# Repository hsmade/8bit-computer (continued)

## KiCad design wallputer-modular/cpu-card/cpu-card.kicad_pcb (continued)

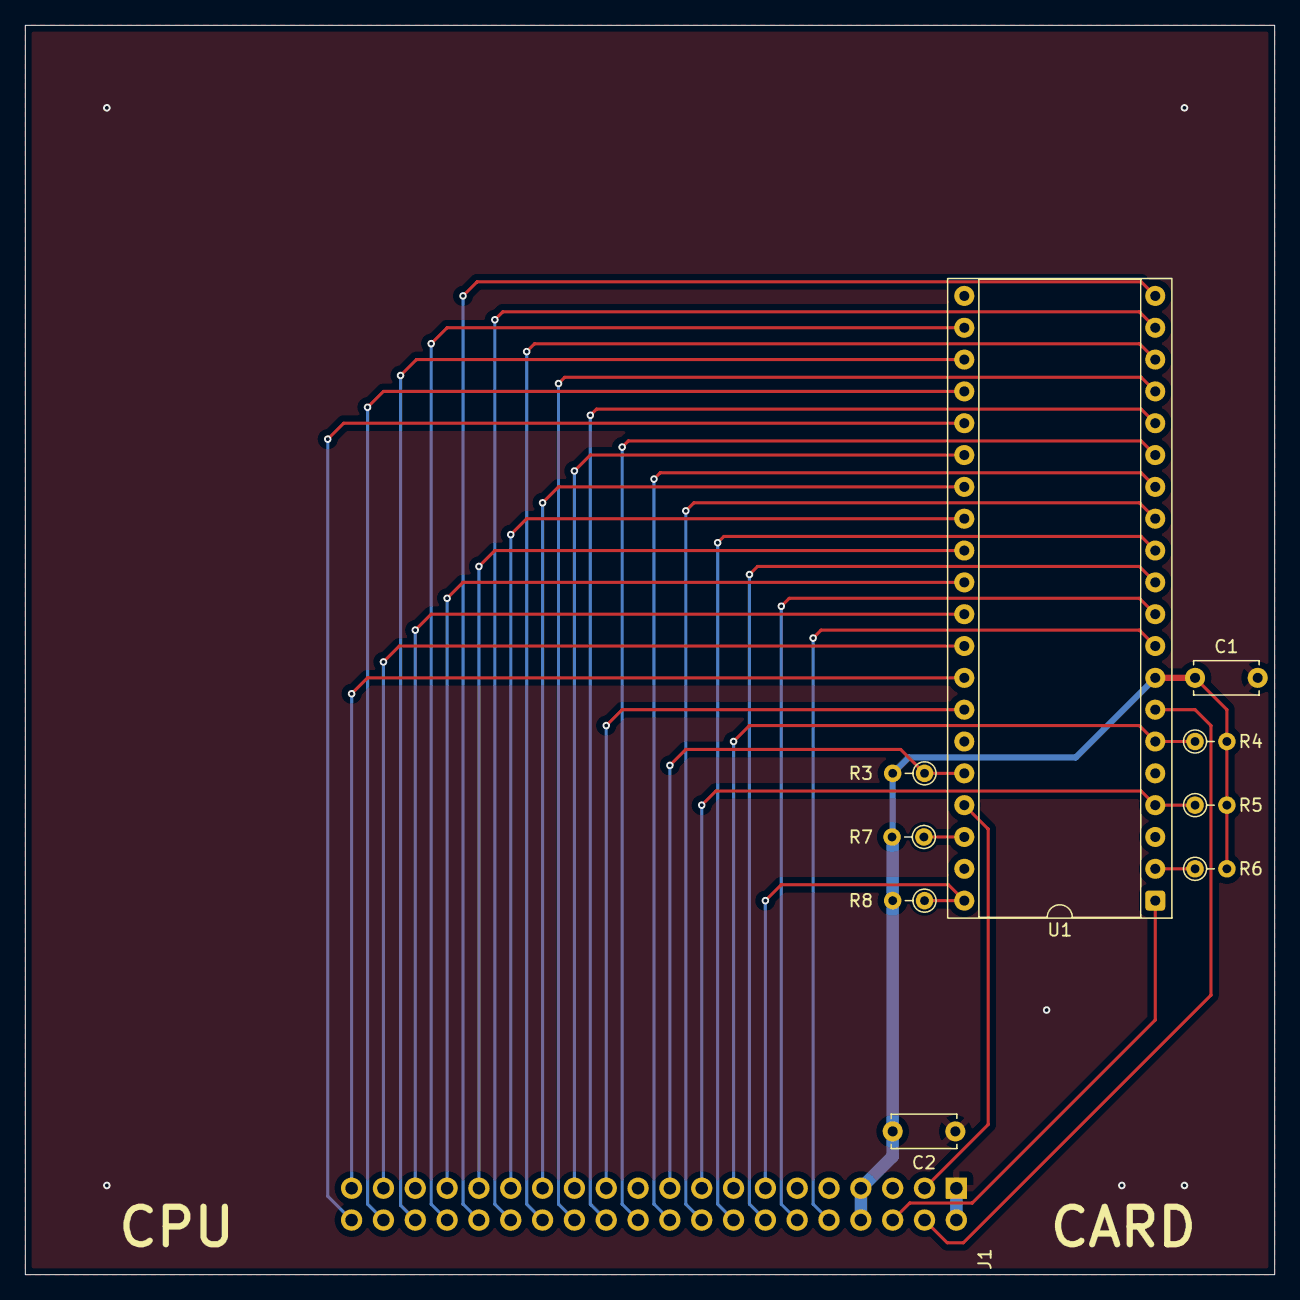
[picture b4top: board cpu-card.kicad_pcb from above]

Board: 2 copper layers, 99.7 x 99.7 mm, 10 parts (0 on the bottom side), 36 nets.

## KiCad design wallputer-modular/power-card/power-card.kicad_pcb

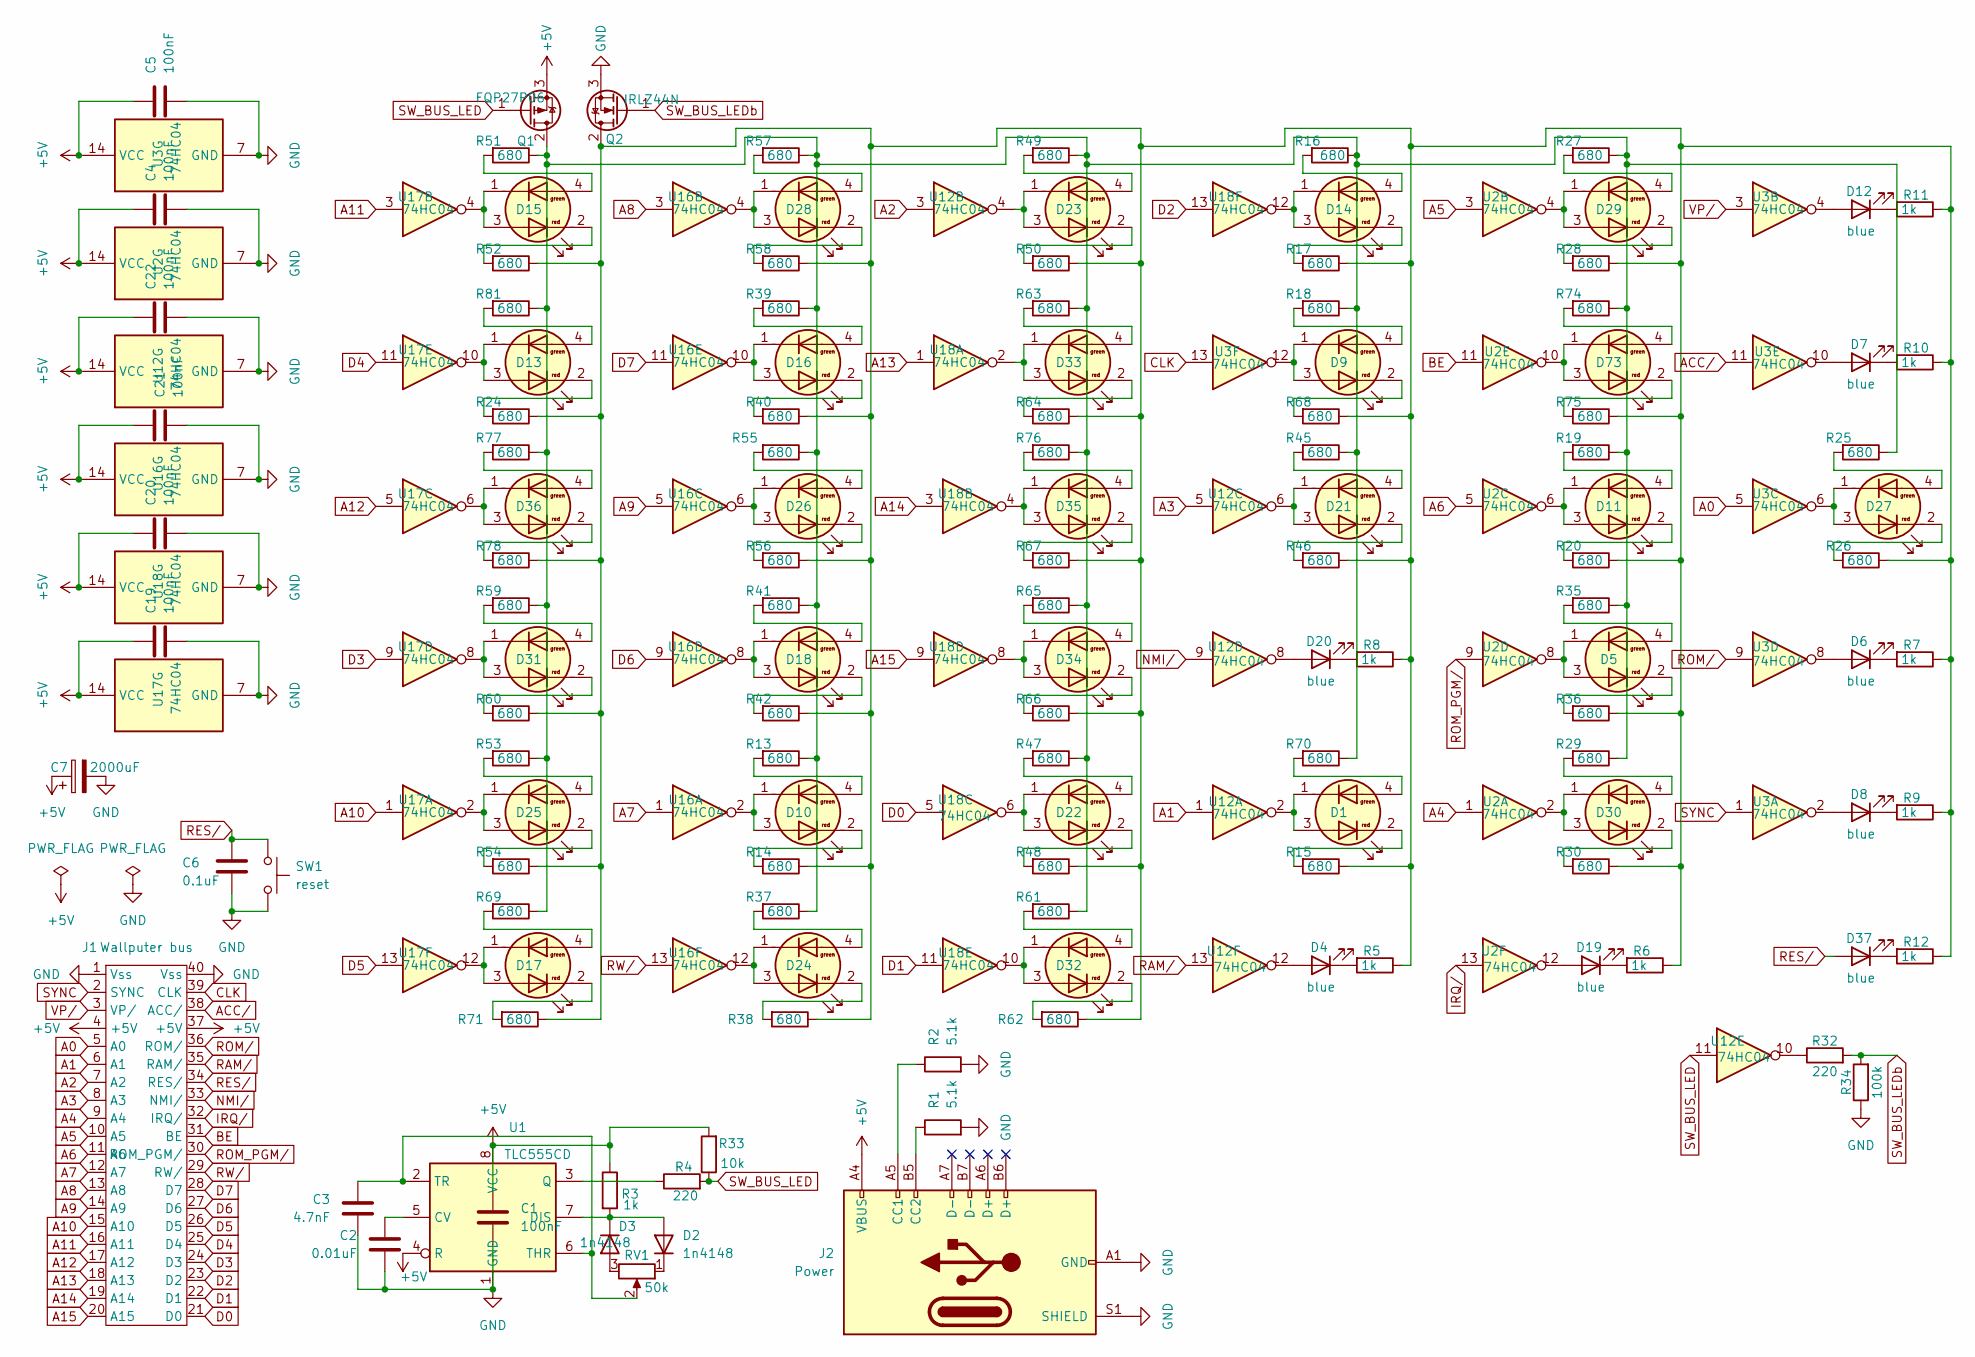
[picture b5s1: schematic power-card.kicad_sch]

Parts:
C1, C4, C5, C19, C20, C21, C22: 100nF; C_Disc_D5.0mm_W2.5mm_P5.00mm
C2: 0.01uF; C_Disc_D5.0mm_W2.5mm_P5.00mm
C3: 4.7nF; C_Disc_D5.0mm_W2.5mm_P5.00mm
C6: 0.1uF; C_Disc_D5.0mm_W2.5mm_P5.00mm
C7: 2000uF; CP_Radial_D18.0mm_P7.50mm
D1, D5, D9, D10, D11, D13, D14, D15, D16, D17, D18, D21, D22, D23, D24, D25, D26, D27, D28, D29, D30, D31, D32, D33, D34, D35, D36, D73: Wallputer_Dual_LED
D2, D3: 1n4148; D_DO-35_SOD27_P7.62mm_Horizontal
D4, D6, D7, D8, D12, D19, D20, D37: blue; LED_1206_3216Metric
J1: Wallputer_Bus_*
J2: Power; USB_C_Receptacle_HRO_TYPE-C-31-M-12
Q1: FQP27P06; TO-220-3_Vertical
Q2: IRLZ44N; TO-220-3_Vertical
R1, R2: 5.1k; R_Axial_DIN0204_L3.6mm_D1.6mm_P2.54mm_Vertical
R3: 1k; R_Axial_DIN0204_L3.6mm_D1.6mm_P2.54mm_Vertical
R4, R32: 220; R_Axial_DIN0204_L3.6mm_D1.6mm_P2.54mm_Vertical
R5, R6, R7, R8, R9, R10, R11, R12: 1k; R_0603_1608Metric
R13, R14, R15, R16, R17, R18, R19, R20, R24, R25, R26, R27, R28, R29, R30, R35, R36, R37, R38, R39, R40, R41, R42, R45, R46, R47, R48, R49, R50, R51, R52, R53, R54, R55, R56, R57, R58, R59, R60, R61, R62, R63, R64, R65, R66, R67, R68, R69, R70, R71, R74, R75, R76, R77, R78, R81: 680; R_0603_1608Metric
R33: 10k; R_Axial_DIN0204_L3.6mm_D1.6mm_P2.54mm_Vertical
R34: 100k; R_Axial_DIN0204_L3.6mm_D1.6mm_P2.54mm_Vertical
RV1: 50k; Potentiometer_Alpha_RD901F-40-00D_Single_Vertical
SW1: reset; SW_PUSH_6mm_H4.3mm
U1: TLC555CD; DIP-8_W7.62mm
U2, U3, U12, U16, U17, U18: 74HC04; SO-14_3.9x8.65mm_P1.27mm

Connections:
+5V: C1.1, C4.1, C5.1, C7.1, C19.1, C20.1, C21.1, C22.1, J1.4 (+5V), J1.37 (+5V), J2.A4 (VBUS), J2.A9 (VBUS), J2.B4 (VBUS), J2.B9 (VBUS), Q1.3 (S), R3.1, R33.2, U1.4 (R), U1.8 (VCC), U2.14 (VCC), U3.14 (VCC), U12.14 (VCC), U16.14 (VCC), U17.14 (VCC), U18.14 (VCC)
A0: J1.5 (A0), U3.5
A1: J1.6 (A1), U12.1
A2: J1.7 (A2), U12.3
A3: J1.8 (A3), U12.5
A4: J1.9 (A4), U2.1
A5: J1.10 (A5), U2.3
A6: J1.11 (A6), U2.5
A7: J1.12 (A7), U16.1
A8: J1.13 (A8), U16.3
A9: J1.14 (A9), U16.5
A10: J1.15 (A10), U17.1
A11: J1.16 (A11), U17.3
A12: J1.17 (A12), U17.5
A13: J1.18 (A13), U18.1
A14: J1.19 (A14), U18.3
A15: J1.20 (A15), U18.9
ACC/: J1.38 (ACC/), U3.11
BE: J1.31 (BE), U2.11
CLK: J1.39 (CLK), U3.13
D0: J1.21 (D0), U18.5
D1: J1.22 (D1), U18.11
D2: J1.23 (D2), U18.13
D3: J1.24 (D3), U17.9
D4: J1.25 (D4), U17.11
D5: J1.26 (D5), U17.13
D6: J1.27 (D6), U16.9
D7: J1.28 (D7), U16.11
GND: C1.2, C2.1, C3.2, C4.2, C5.2, C6.2, C7.2, C19.2, C20.2, C21.2, C22.2, J1.1 (Vss), J1.40 (Vss), J2.A1 (GND), J2.A12 (GND), J2.B1 (GND), J2.B12 (GND), J2.S1 (SHIELD), Q2.3 (S), R1.2, R2.2, R34.1, SW1.2, U1.1 (GND), U2.7 (GND), U3.7 (GND), U12.7 (GND), U16.7 (GND), U17.7 (GND), U18.7 (GND)
IRQ/: J1.32 (IRQ/), U2.13
NMI/: J1.33 (NMI/), U12.9
unnamed: D1.4 (Green_A), R70.2
unnamed: D1.1 (Green_K), D1.3 (Red_A), U12.2
unnamed: D1.2 (Red_K), R15.2
unnamed: D2.2 (A), D3.1 (K), R3.2, U1.7 (DIS)
unnamed: D2.1 (K), RV1.1
unnamed: D3.2 (A), RV1.3
unnamed: D4.2 (A), U12.12
unnamed: D4.1 (K), R5.2
unnamed: D5.4 (Green_A), R35.2
unnamed: D5.1 (Green_K), D5.3 (Red_A), U2.8
unnamed: D5.2 (Red_K), R36.2
unnamed: D6.2 (A), U3.8
unnamed: D6.1 (K), R7.2
unnamed: D7.2 (A), U3.10
unnamed: D7.1 (K), R10.2
unnamed: D8.2 (A), U3.2
unnamed: D8.1 (K), R9.2
unnamed: D9.4 (Green_A), R18.2
unnamed: D9.1 (Green_K), D9.3 (Red_A), U3.12
unnamed: D9.2 (Red_K), R68.2
unnamed: D10.4 (Green_A), R13.2
unnamed: D10.1 (Green_K), D10.3 (Red_A), U16.2
unnamed: D10.2 (Red_K), R14.2
unnamed: D11.4 (Green_A), R19.2
unnamed: D11.1 (Green_K), D11.3 (Red_A), U2.6
unnamed: D11.2 (Red_K), R20.2
unnamed: D12.2 (A), U3.4
unnamed: D12.1 (K), R11.2
unnamed: D13.4 (Green_A), R81.2
unnamed: D13.1 (Green_K), D13.3 (Red_A), U17.10
unnamed: D13.2 (Red_K), R24.2
unnamed: D14.4 (Green_A), R16.2
unnamed: D14.1 (Green_K), D14.3 (Red_A), U18.12
unnamed: D14.2 (Red_K), R17.2
unnamed: D15.4 (Green_A), R51.2
unnamed: D15.1 (Green_K), D15.3 (Red_A), U17.4
unnamed: D15.2 (Red_K), R52.2
unnamed: D16.4 (Green_A), R39.2
unnamed: D16.1 (Green_K), D16.3 (Red_A), U16.10
unnamed: D16.2 (Red_K), R40.2
unnamed: D17.4 (Green_A), R69.2
unnamed: D17.1 (Green_K), D17.3 (Red_A), U17.12
unnamed: D17.2 (Red_K), R71.2
unnamed: D18.4 (Green_A), R41.2
unnamed: D18.1 (Green_K), D18.3 (Red_A), U16.8
unnamed: D18.2 (Red_K), R42.2
unnamed: D19.2 (A), U2.12
unnamed: D19.1 (K), R6.2
unnamed: D20.2 (A), U12.8
unnamed: D20.1 (K), R8.2
unnamed: D21.4 (Green_A), R45.2
unnamed: D21.1 (Green_K), D21.3 (Red_A), U12.6
unnamed: D21.2 (Red_K), R46.2
unnamed: D22.4 (Green_A), R47.2
unnamed: D22.1 (Green_K), D22.3 (Red_A), U18.6
unnamed: D22.2 (Red_K), R48.2
unnamed: D23.4 (Green_A), R49.2
unnamed: D23.1 (Green_K), D23.3 (Red_A), U12.4
unnamed: D23.2 (Red_K), R50.2
unnamed: D24.4 (Green_A), R37.2
unnamed: D24.1 (Green_K), D24.3 (Red_A), U16.12
unnamed: D24.2 (Red_K), R38.2
unnamed: D25.4 (Green_A), R53.2
unnamed: D25.1 (Green_K), D25.3 (Red_A), U17.2
unnamed: D25.2 (Red_K), R54.2
unnamed: D26.4 (Green_A), R55.2
unnamed: D26.1 (Green_K), D26.3 (Red_A), U16.6
unnamed: D26.2 (Red_K), R56.2
unnamed: D27.4 (Green_A), R25.2
unnamed: D27.1 (Green_K), D27.3 (Red_A), U3.6
unnamed: D27.2 (Red_K), R26.2
unnamed: D28.4 (Green_A), R57.2
unnamed: D28.1 (Green_K), D28.3 (Red_A), U16.4
unnamed: D28.2 (Red_K), R58.2
unnamed: D29.4 (Green_A), R27.2
unnamed: D29.1 (Green_K), D29.3 (Red_A), U2.4
unnamed: D29.2 (Red_K), R28.2
unnamed: D30.4 (Green_A), R29.2
unnamed: D30.1 (Green_K), D30.3 (Red_A), U2.2
unnamed: D30.2 (Red_K), R30.2
unnamed: D31.4 (Green_A), R59.2
unnamed: D31.1 (Green_K), D31.3 (Red_A), U17.8
unnamed: D31.2 (Red_K), R60.2
unnamed: D32.4 (Green_A), R61.2
unnamed: D32.1 (Green_K), D32.3 (Red_A), U18.10
unnamed: D32.2 (Red_K), R62.2
unnamed: D33.4 (Green_A), R63.2
unnamed: D33.1 (Green_K), D33.3 (Red_A), U18.2
unnamed: D33.2 (Red_K), R64.2
unnamed: D34.4 (Green_A), R65.2
unnamed: D34.1 (Green_K), D34.3 (Red_A), U18.8
unnamed: D34.2 (Red_K), R66.2
unnamed: D35.4 (Green_A), R76.2
unnamed: D35.1 (Green_K), D35.3 (Red_A), U18.4
unnamed: D35.2 (Red_K), R67.2
unnamed: D36.4 (Green_A), R77.2
unnamed: D36.1 (Green_K), D36.3 (Red_A), U17.6
unnamed: D36.2 (Red_K), R78.2
unnamed: D37.1 (K), R12.2
unnamed: D73.4 (Green_A), R74.2
unnamed: D73.1 (Green_K), D73.3 (Red_A), U2.10
unnamed: D73.2 (Red_K), R75.2
unnamed: J2.A5 (CC1), R2.1
unnamed: J2.B5 (CC2), R1.1
unnamed: Q1.2 (D), R13.1, R16.1, R18.1, R19.1, R25.1, R27.1, R29.1, R35.1, R37.1, R39.1, R41.1, R45.1, R47.1, R49.1, R51.1, R53.1, R55.1, R57.1, R59.1, R61.1, R63.1, R65.1, R69.1, R70.1, R74.1, R76.1, R77.1, R81.1
unnamed: Q2.2 (D), R5.1, R6.1, R7.1, R8.1, R9.1, R10.1, R11.1, R12.1, R14.1, R15.1, R17.1, R20.1, R24.1, R26.1, R28.1, R30.1, R36.1, R38.1, R40.1, R42.1, R46.1, R48.1, R50.1, R52.1, R54.1, R56.1, R58.1, R60.1, R62.1, R64.1, R66.1, R67.1, R68.1, R71.1, R75.1, R78.1
unnamed: R32.1, U12.10
unnamed: C2.2, U1.5 (CV)
unnamed: R4.1, U1.3 (Q)
unnamed: C3.1, RV1.2, U1.2 (TR), U1.6 (THR)
RAM/: J1.35 (RAM/), U12.13
RES/: C6.1, D37.2 (A), J1.34 (RES/), SW1.1
ROM_PGM/: J1.30 (ROM_PGM/), U2.9
ROM/: J1.36 (ROM/), U3.9
RW/: J1.29 (RW/), U16.13
SW_BUS_LED: Q1.1 (G), R4.2, R33.1, U12.11
SW_BUS_LEDb: Q2.1 (G), R32.2, R34.2
SYNC: J1.2 (SYNC), U3.1
VP/: J1.3 (VP/), U3.3

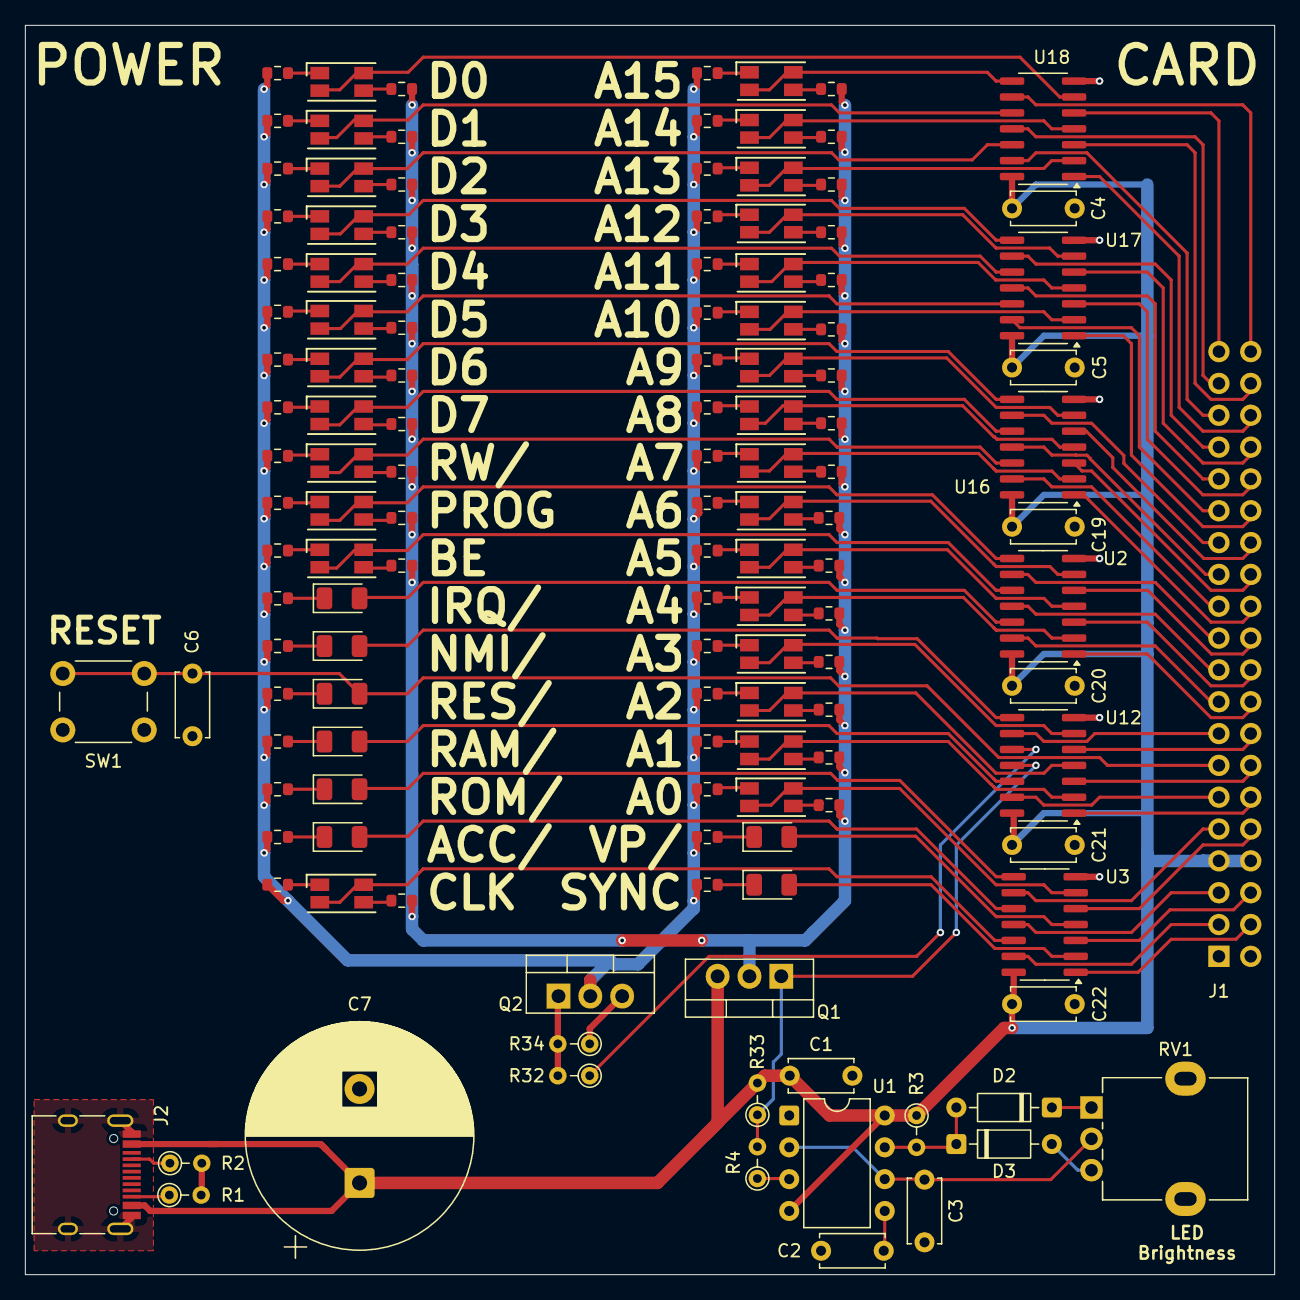
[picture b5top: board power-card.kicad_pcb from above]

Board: 2 copper layers, 99.7 x 99.7 mm, 133 parts (0 on the bottom side), 150 nets.

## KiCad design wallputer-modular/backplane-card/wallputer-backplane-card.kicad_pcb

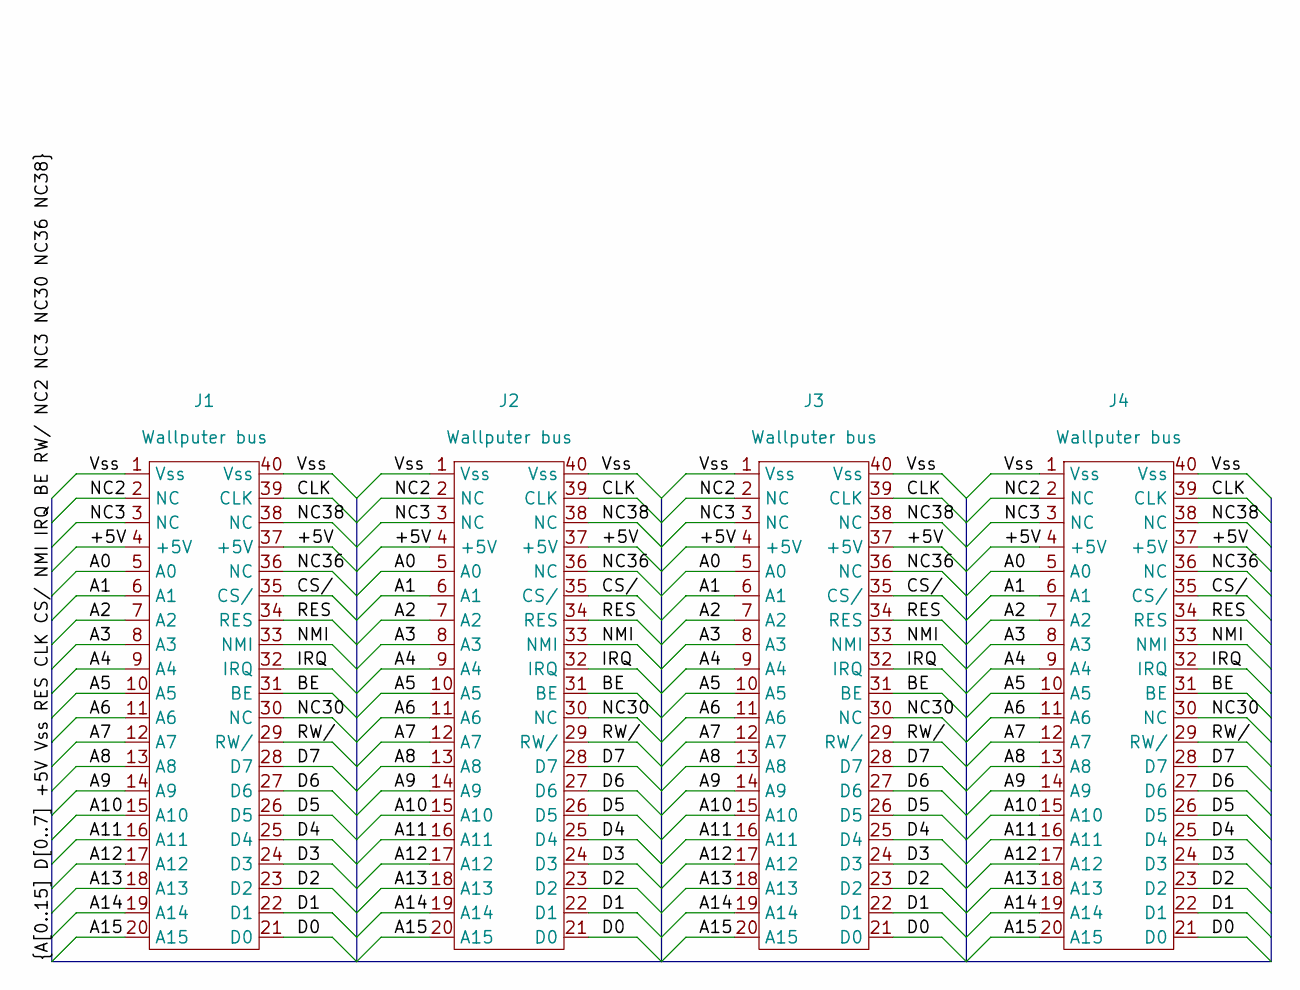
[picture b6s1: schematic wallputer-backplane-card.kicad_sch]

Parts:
J1: Wallputer_Bus_Header
J2, J3, J4: Wallputer_Bus_Socket

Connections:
/+5V: J1.4 (+5V), J1.37 (+5V), J2.4 (+5V), J2.37 (+5V), J3.4 (+5V), J3.37 (+5V), J4.4 (+5V), J4.37 (+5V)
/A0: J1.5 (A0), J2.5 (A0), J3.5 (A0), J4.5 (A0)
/A1: J1.6 (A1), J2.6 (A1), J3.6 (A1), J4.6 (A1)
/A2: J1.7 (A2), J2.7 (A2), J3.7 (A2), J4.7 (A2)
/A3: J1.8 (A3), J2.8 (A3), J3.8 (A3), J4.8 (A3)
/A4: J1.9 (A4), J2.9 (A4), J3.9 (A4), J4.9 (A4)
/A5: J1.10 (A5), J2.10 (A5), J3.10 (A5), J4.10 (A5)
/A6: J1.11 (A6), J2.11 (A6), J3.11 (A6), J4.11 (A6)
/A7: J1.12 (A7), J2.12 (A7), J3.12 (A7), J4.12 (A7)
/A8: J1.13 (A8), J2.13 (A8), J3.13 (A8), J4.13 (A8)
/A9: J1.14 (A9), J2.14 (A9), J3.14 (A9), J4.14 (A9)
/A10: J1.15 (A10), J2.15 (A10), J3.15 (A10), J4.15 (A10)
/A11: J1.16 (A11), J2.16 (A11), J3.16 (A11), J4.16 (A11)
/A12: J1.17 (A12), J2.17 (A12), J3.17 (A12), J4.17 (A12)
/A13: J1.18 (A13), J2.18 (A13), J3.18 (A13), J4.18 (A13)
/A14: J1.19 (A14), J2.19 (A14), J3.19 (A14), J4.19 (A14)
/A15: J1.20 (A15), J2.20 (A15), J3.20 (A15), J4.20 (A15)
/BE: J1.31 (BE), J2.31 (BE), J3.31 (BE), J4.31 (BE)
/CLK: J1.39 (CLK), J2.39 (CLK), J3.39 (CLK), J4.39 (CLK)
/CS/: J1.35 (CS/), J2.35 (CS/), J3.35 (CS/), J4.35 (CS/)
/D0: J1.21 (D0), J2.21 (D0), J3.21 (D0), J4.21 (D0)
/D1: J1.22 (D1), J2.22 (D1), J3.22 (D1), J4.22 (D1)
/D2: J1.23 (D2), J2.23 (D2), J3.23 (D2), J4.23 (D2)
/D3: J1.24 (D3), J2.24 (D3), J3.24 (D3), J4.24 (D3)
/D4: J1.25 (D4), J2.25 (D4), J3.25 (D4), J4.25 (D4)
/D5: J1.26 (D5), J2.26 (D5), J3.26 (D5), J4.26 (D5)
/D6: J1.27 (D6), J2.27 (D6), J3.27 (D6), J4.27 (D6)
/D7: J1.28 (D7), J2.28 (D7), J3.28 (D7), J4.28 (D7)
/IRQ: J1.32 (IRQ), J2.32 (IRQ), J3.32 (IRQ), J4.32 (IRQ)
/NC2: J1.2 (NC), J2.2 (NC), J3.2 (NC), J4.2 (NC)
/NC3: J1.3 (NC), J2.3 (NC), J3.3 (NC), J4.3 (NC)
/NC30: J1.30 (NC), J2.30 (NC), J3.30 (NC), J4.30 (NC)
/NC36: J1.36 (NC), J2.36 (NC), J3.36 (NC), J4.36 (NC)
/NC38: J1.38 (NC), J2.38 (NC), J3.38 (NC), J4.38 (NC)
/NMI: J1.33 (NMI), J2.33 (NMI), J3.33 (NMI), J4.33 (NMI)
/RES: J1.34 (RES), J2.34 (RES), J3.34 (RES), J4.34 (RES)
/RW/: J1.29 (RW/), J2.29 (RW/), J3.29 (RW/), J4.29 (RW/)
/Vss: J1.1 (Vss), J1.40 (Vss), J2.1 (Vss), J2.40 (Vss), J3.1 (Vss), J3.40 (Vss), J4.1 (Vss), J4.40 (Vss)

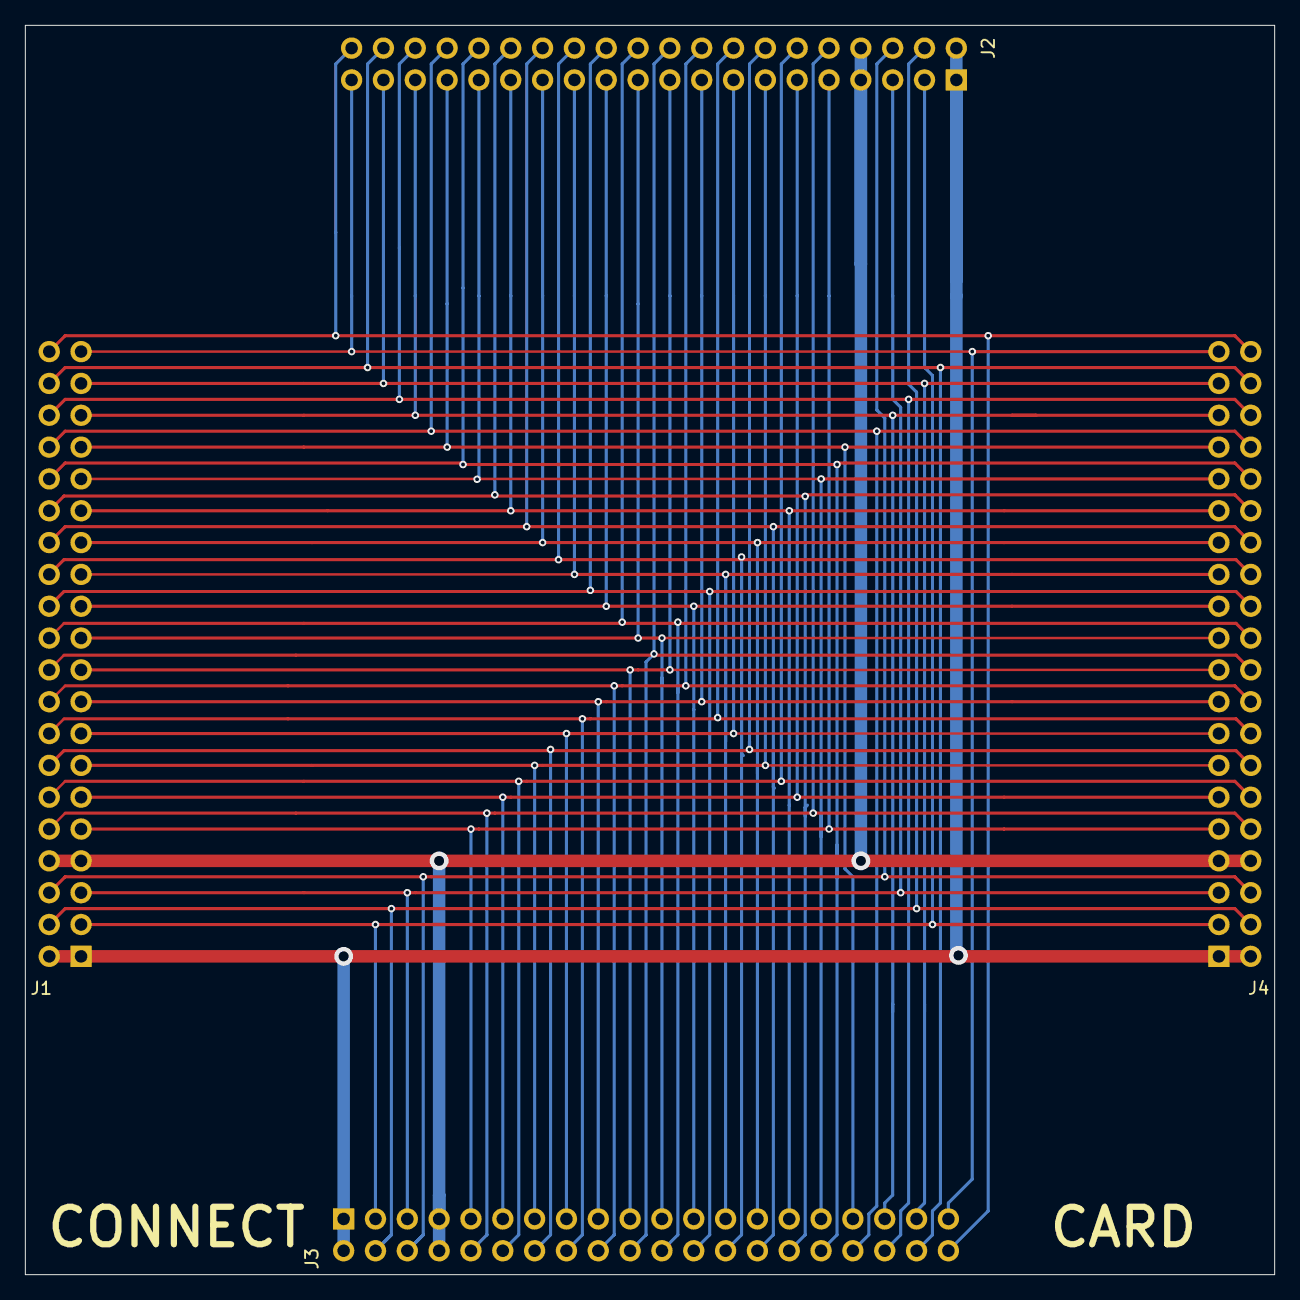
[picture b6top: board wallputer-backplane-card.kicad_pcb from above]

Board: 2 copper layers, 99.7 x 99.7 mm, 4 parts (0 on the bottom side), 38 nets.

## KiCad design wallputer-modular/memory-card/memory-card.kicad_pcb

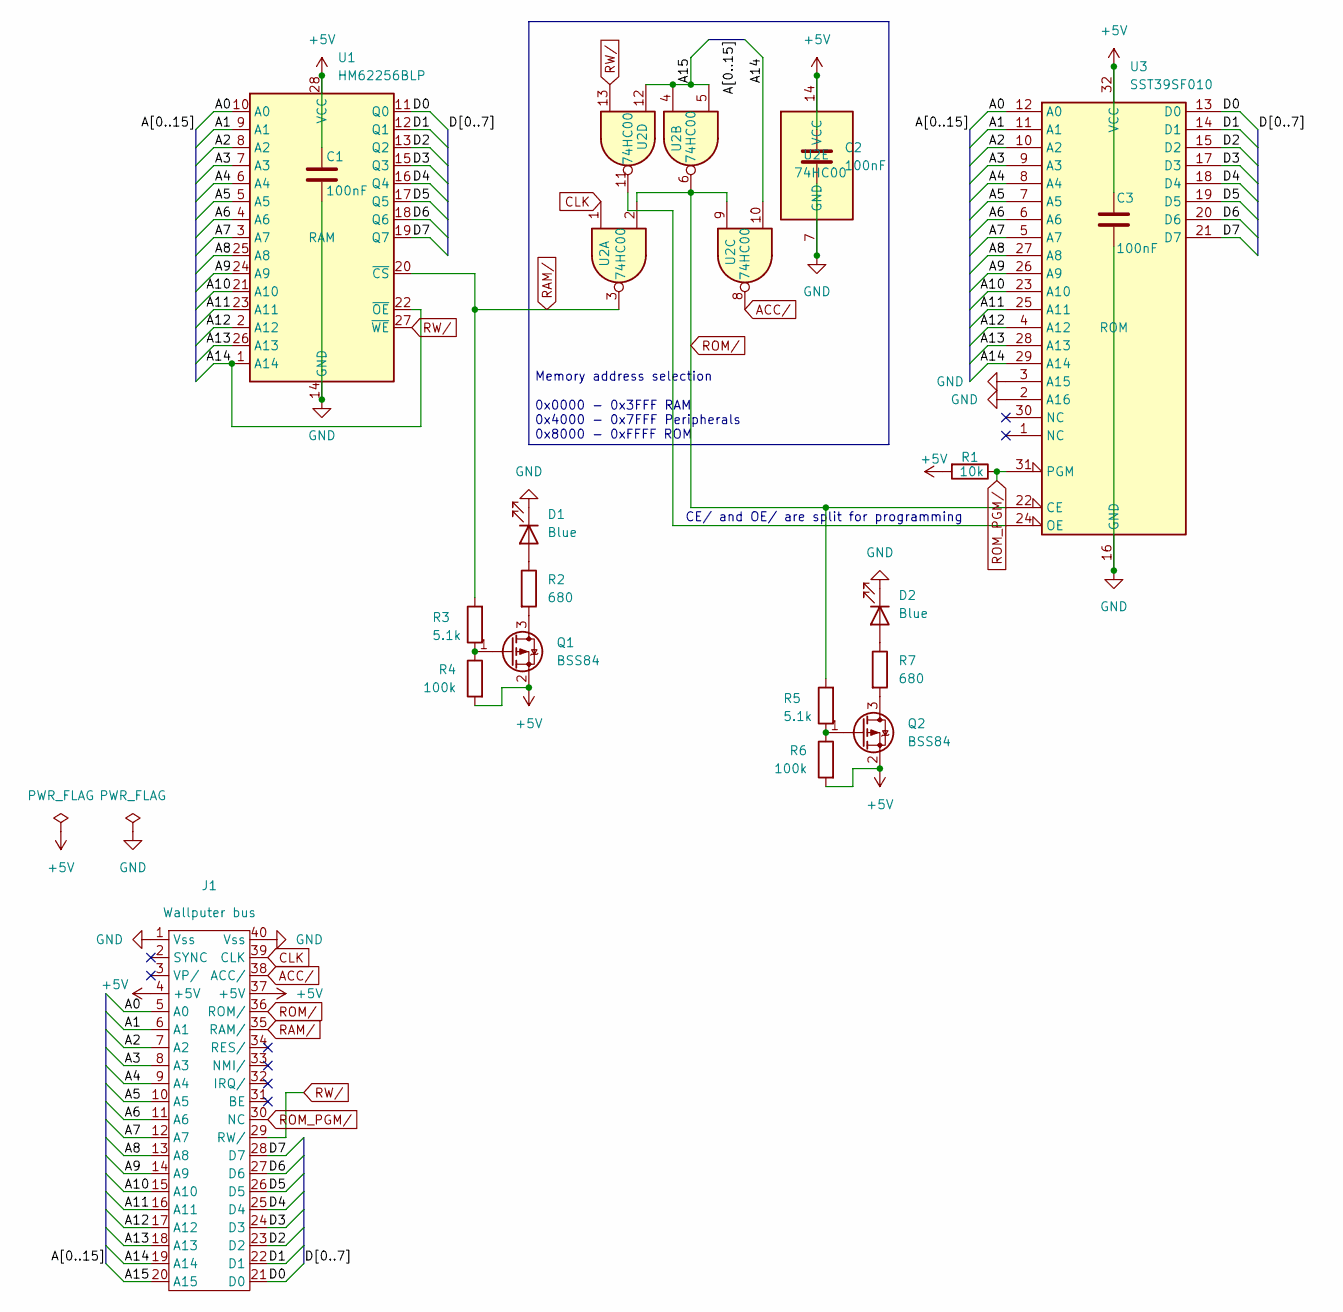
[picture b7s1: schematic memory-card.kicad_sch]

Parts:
C1, C2, C3: 100nF; C_Disc_D5.0mm_W2.5mm_P5.00mm
D1, D2: Blue; LED_1206_3216Metric
J1: Wallputer_Bus_Header
Q1, Q2: BSS84; SOT-23
R1: 10k; R_Axial_DIN0204_L3.6mm_D1.6mm_P2.54mm_Vertical
R2, R7: 680; R_0603_1608Metric
R3, R5: 5.1k; R_0603_1608Metric
R4, R6: 100k; R_0603_1608Metric
U1: HM62256BLP; DIP-28_W7.62mm_Socket
U2: 74HC00; DIP-14_W7.62mm_Socket
U3: SST39SF010; DIP-32_W15.24mm_Socket

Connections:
+5V: C1.1, C2.1, C3.1, J1.4 (+5V), J1.37 (+5V), Q1.2 (S), Q2.2 (S), R1.2, R4.2, R6.2, U1.28 (VCC), U2.14 (VCC), U3.32 (VCC)
/A0: J1.5 (A0), U1.10 (A0), U3.12 (A0)
/A1: J1.6 (A1), U1.9 (A1), U3.11 (A1)
/A2: J1.7 (A2), U1.8 (A2), U3.10 (A2)
/A3: J1.8 (A3), U1.7 (A3), U3.9 (A3)
/A4: J1.9 (A4), U1.6 (A4), U3.8 (A4)
/A5: J1.10 (A5), U1.5 (A5), U3.7 (A5)
/A6: J1.11 (A6), U1.4 (A6), U3.6 (A6)
/A7: J1.12 (A7), U1.3 (A7), U3.5 (A7)
/A8: J1.13 (A8), U1.25 (A8), U3.27 (A8)
/A9: J1.14 (A9), U1.24 (A9), U3.26 (A9)
/A10: J1.15 (A10), U1.21 (A10), U3.23 (A10)
/A11: J1.16 (A11), U1.23 (A11), U3.25 (A11)
/A12: J1.17 (A12), U1.2 (A12), U3.4 (A12)
/A13: J1.18 (A13), U1.26 (A13), U3.28 (A13)
/A14: J1.19 (A14), U1.1 (A14), U1.22 (~OE), U2.10, U3.29 (A14)
/A15: J1.20 (A15), U2.4, U2.5, U2.12
/D0: J1.21 (D0), U1.11 (Q0), U3.13 (D0)
/D1: J1.22 (D1), U1.12 (Q1), U3.14 (D1)
/D2: J1.23 (D2), U1.13 (Q2), U3.15 (D2)
/D3: J1.24 (D3), U1.15 (Q3), U3.17 (D3)
/D4: J1.25 (D4), U1.16 (Q4), U3.18 (D4)
/D5: J1.26 (D5), U1.17 (Q5), U3.19 (D5)
/D6: J1.27 (D6), U1.18 (Q6), U3.20 (D6)
/D7: J1.28 (D7), U1.19 (Q7), U3.21 (D7)
ACC/: J1.38 (ACC/), U2.8
CLK: J1.39 (CLK), U2.1
GND: C1.2, C2.2, C3.2, D1.1 (K), D2.1 (K), J1.1 (Vss), J1.40 (Vss), U1.14 (GND), U2.7 (GND), U3.2 (A16), U3.3 (A15), U3.16 (GND)
unnamed: D1.2 (A), R2.1
unnamed: D2.2 (A), R7.1
unnamed: Q1.3 (D), R2.2
unnamed: Q1.1 (G), R3.1, R4.1
unnamed: Q2.3 (D), R7.2
unnamed: Q2.1 (G), R5.1, R6.1
unnamed: U2.11, U3.24 (OE)
RAM/: J1.35 (RAM/), R3.2, U1.20 (~CS), U2.3
ROM_PGM/: J1.30 (NC), R1.1, U3.31 (PGM)
ROM/: J1.36 (ROM/), R5.2, U2.2, U2.6, U2.9, U3.22 (CE)
RW/: J1.29 (RW/), U1.27 (~WE), U2.13

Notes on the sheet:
CE/ and OE/ are split for programming
Memory address selection 0x0000 - 0x3FFF RAM 0x4000 - 0x7FFF Peripherals 0x8000 - 0xFFFF ROM

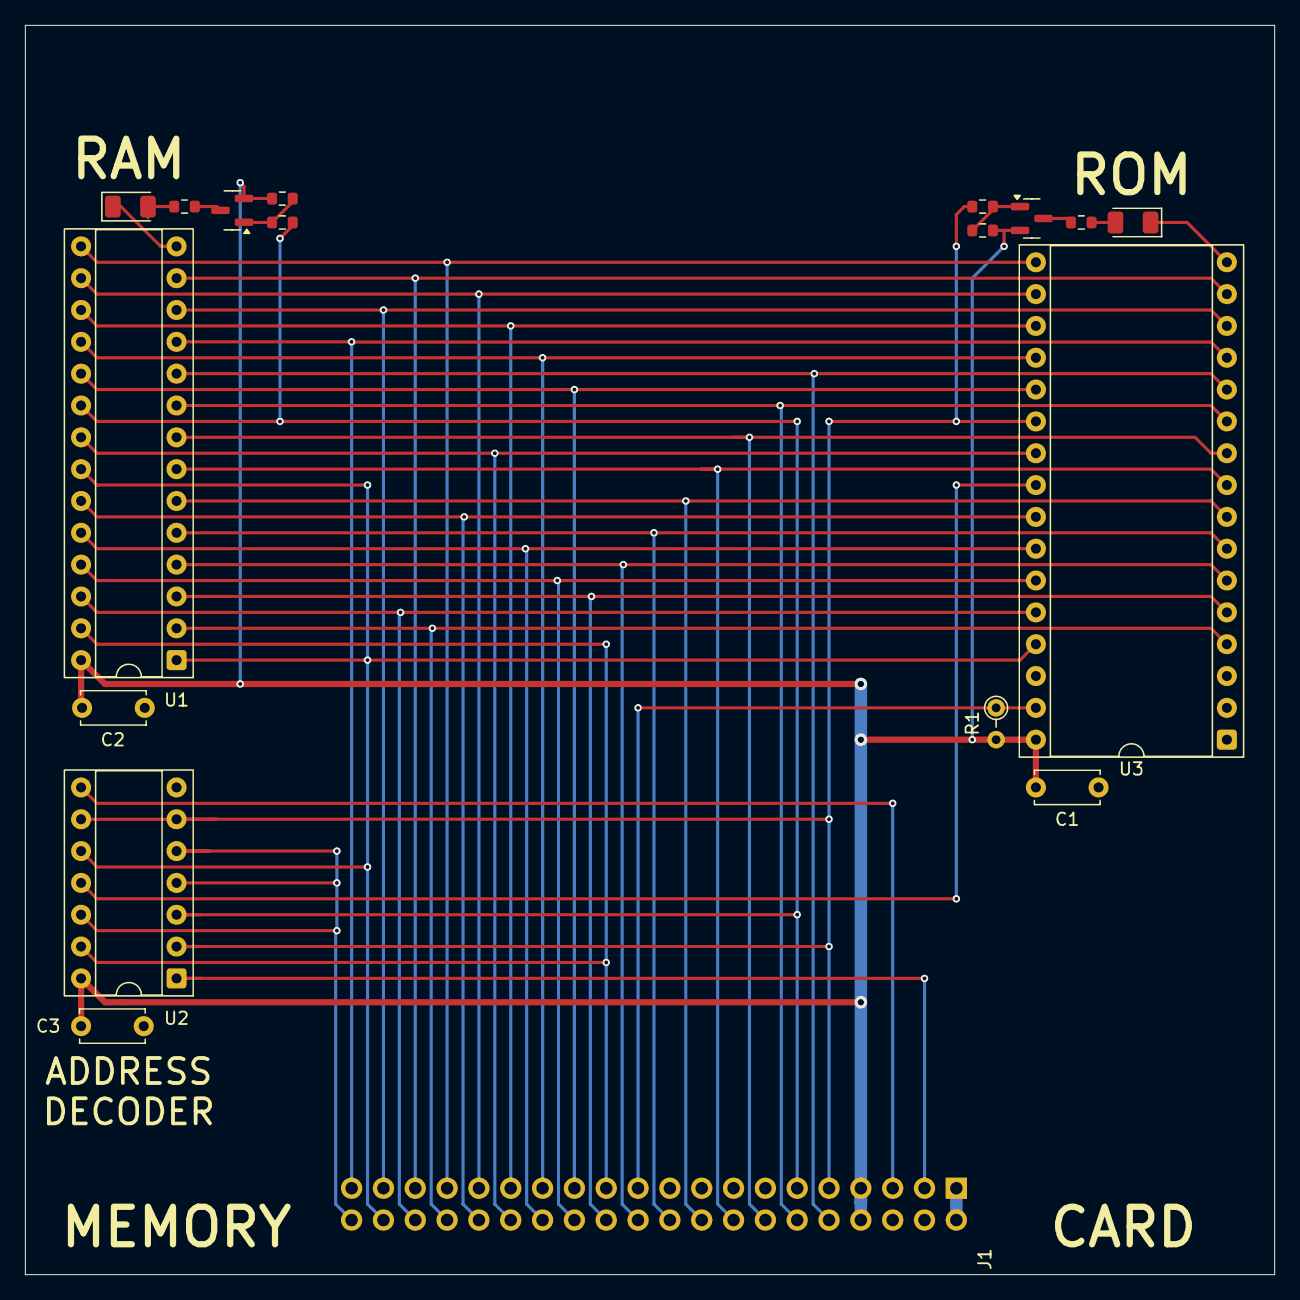
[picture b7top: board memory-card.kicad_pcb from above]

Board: 2 copper layers, 99.7 x 99.7 mm, 18 parts (0 on the bottom side), 39 nets.
